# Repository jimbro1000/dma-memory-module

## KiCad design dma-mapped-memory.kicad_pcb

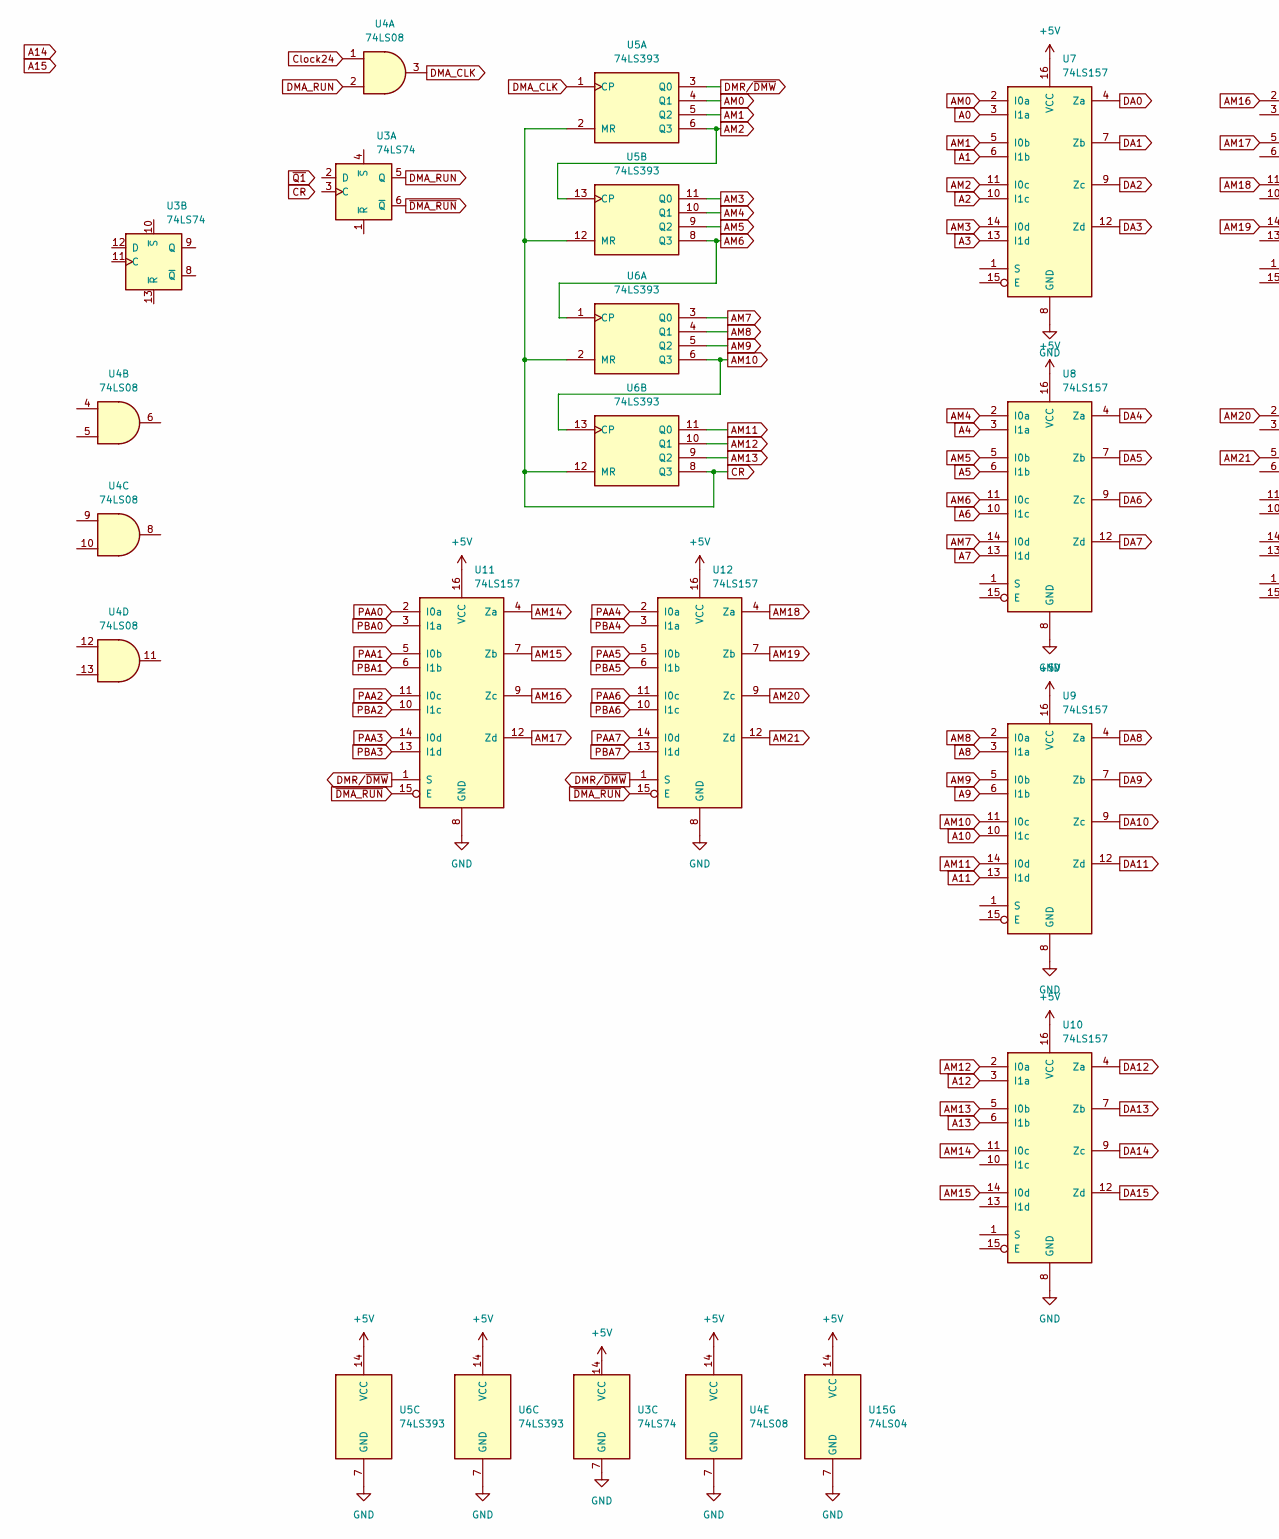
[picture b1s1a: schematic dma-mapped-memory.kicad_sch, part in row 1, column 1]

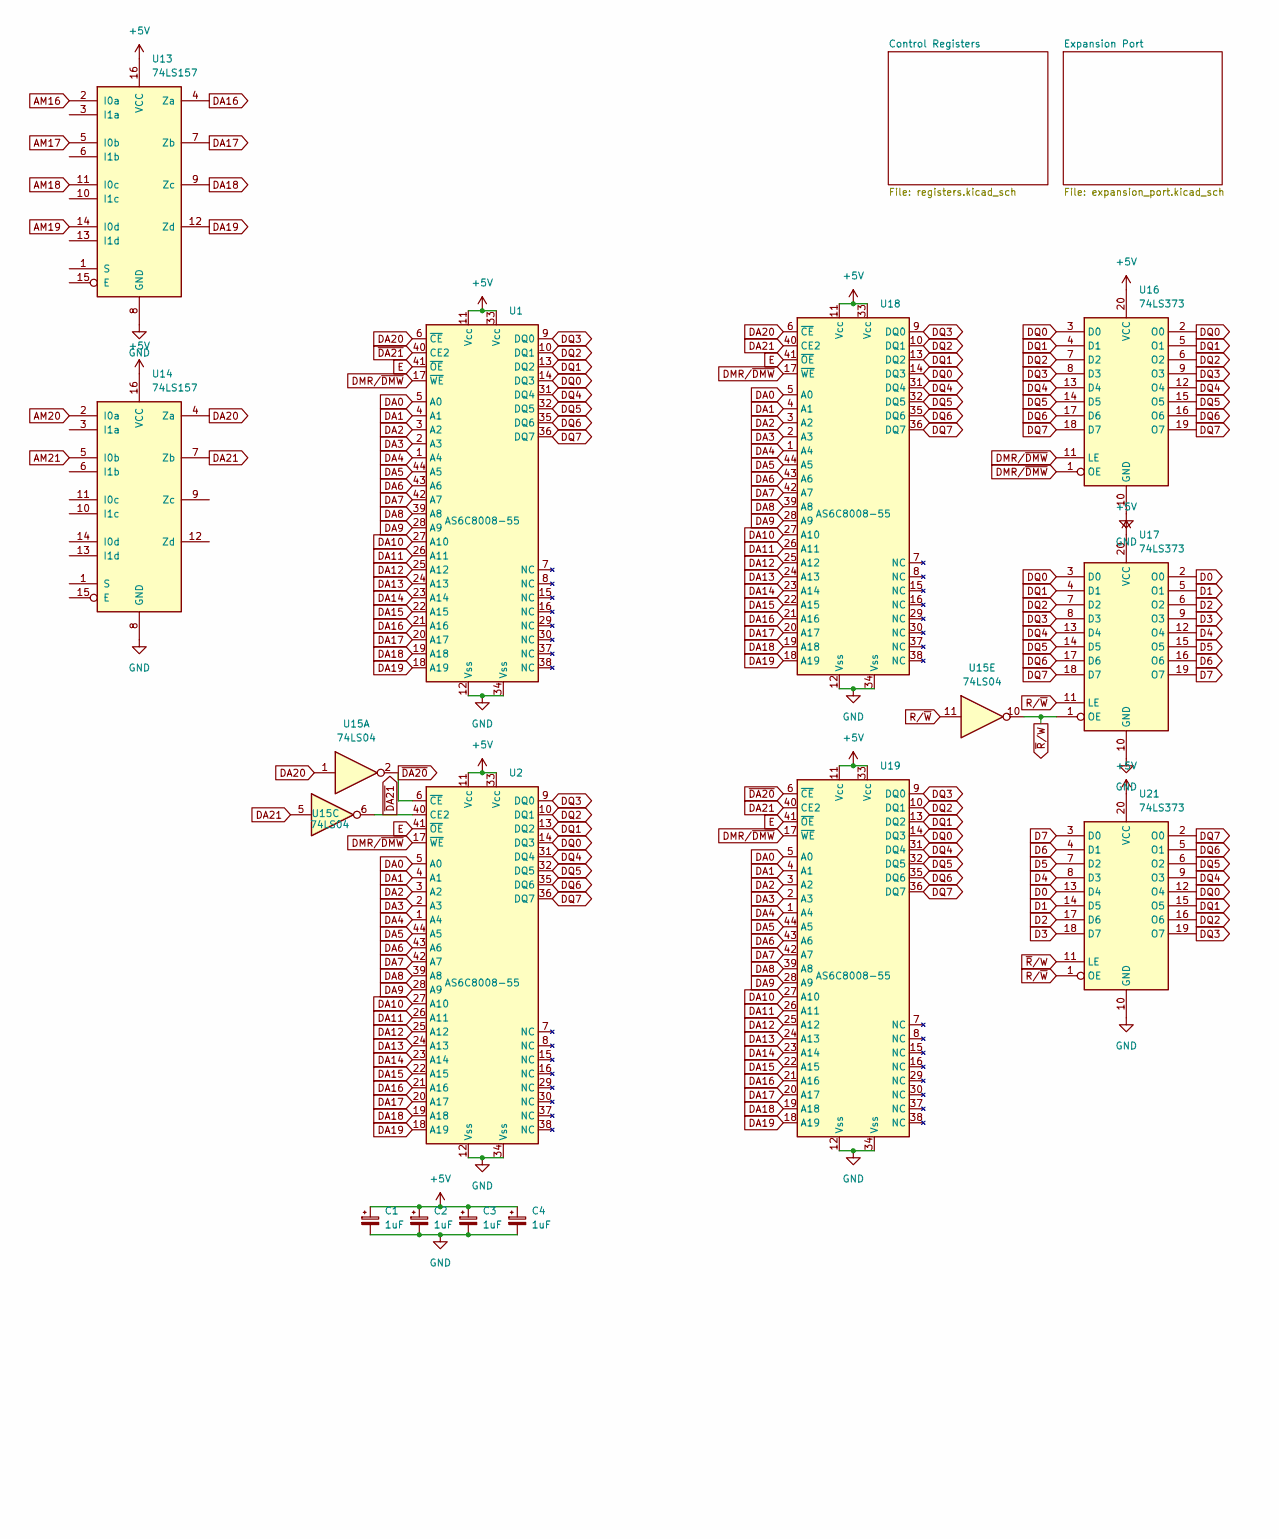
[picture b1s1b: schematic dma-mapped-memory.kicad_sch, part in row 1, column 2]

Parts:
C1, C2, C3, C4: 1uF; CP_EIA-3216-18_Kemet-A_Pad1.58x1.35mm_HandSolder
U1, U2, U18, U19: AS6C8008-55; TSOP-II-44_10.16x18.41mm_P0.8mm
U3: 74LS74; SOIC-14_3.9x8.7mm_P1.27mm
U4: 74LS08; SOIC-14_3.9x8.7mm_P1.27mm
U5, U6: 74LS393; SOIC-14_3.9x8.7mm_P1.27mm
U7, U8, U9, U10, U11, U12, U13, U14: 74LS157; SOIC-16_3.9x9.9mm_P1.27mm
U15: 74LS04; SOIC-14_3.9x8.7mm_P1.27mm
U16, U17, U21: 74LS373; SOIC-20W_7.5x12.8mm_P1.27mm

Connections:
+5V: C1.1, C2.1, C3.1, C4.1, U1.11 (Vcc), U1.33 (Vcc), U2.11 (Vcc), U2.33 (Vcc), U3.14 (VCC), U4.14 (VCC), U5.14 (VCC), U6.14 (VCC), U7.16 (VCC), U8.16 (VCC), U9.16 (VCC), U10.16 (VCC), U11.16 (VCC), U12.16 (VCC), U13.16 (VCC), U14.16 (VCC), U15.14 (VCC), U16.20 (VCC), U17.20 (VCC), U18.11 (Vcc), U18.33 (Vcc), U19.11 (Vcc), U19.33 (Vcc), U21.20 (VCC); also elsewhere on the board
A0: U7.3 (I1a); also elsewhere on the board
A1: U7.6 (I1b); also elsewhere on the board
A2: U7.10 (I1c); also elsewhere on the board
A3: U7.13 (I1d); also elsewhere on the board
A4: U8.3 (I1a); also elsewhere on the board
A5: U8.6 (I1b); also elsewhere on the board
A6: U8.10 (I1c); also elsewhere on the board
A7: U8.13 (I1d); also elsewhere on the board
A8: U9.3 (I1a); also elsewhere on the board
A9: U9.6 (I1b); also elsewhere on the board
A10: U9.10 (I1c); also elsewhere on the board
A11: U9.13 (I1d); also elsewhere on the board
A12: U10.3 (I1a); also elsewhere on the board
A13: U10.6 (I1b); also elsewhere on the board
AM0: U5.4 (Q1), U7.2 (I0a)
AM1: U5.5 (Q2), U7.5 (I0b)
AM2: U5.6 (Q3), U5.13 (CP), U7.11 (I0c)
AM3: U5.11 (Q0), U7.14 (I0d)
AM4: U5.10 (Q1), U8.2 (I0a)
AM5: U5.9 (Q2), U8.5 (I0b)
AM6: U5.8 (Q3), U6.1 (CP), U8.11 (I0c)
AM7: U6.3 (Q0), U8.14 (I0d)
AM8: U6.4 (Q1), U9.2 (I0a)
AM9: U6.5 (Q2), U9.5 (I0b)
AM10: U6.6 (Q3), U6.13 (CP), U9.11 (I0c)
AM11: U6.11 (Q0), U9.14 (I0d)
AM12: U6.10 (Q1), U10.2 (I0a)
AM13: U6.9 (Q2), U10.5 (I0b)
AM14: U10.11 (I0c), U11.4 (Za)
AM15: U10.14 (I0d), U11.7 (Zb)
AM16: U11.9 (Zc), U13.2 (I0a)
AM17: U11.12 (Zd), U13.5 (I0b)
AM18: U12.4 (Za), U13.11 (I0c)
AM19: U12.7 (Zb), U13.14 (I0d)
AM20: U12.9 (Zc), U14.2 (I0a)
AM21: U12.12 (Zd), U14.5 (I0b)
CR: U5.2 (MR), U5.12 (MR), U6.2 (MR), U6.8 (Q3), U6.12 (MR)
Clock24: U4.1; also elsewhere on the board
D0: U17.2 (O0), U21.13 (D4); also elsewhere on the board
D1: U17.5 (O1), U21.14 (D5); also elsewhere on the board
D2: U17.6 (O2), U21.17 (D6); also elsewhere on the board
D3: U17.9 (O3), U21.18 (D7); also elsewhere on the board
D4: U17.12 (O4), U21.8 (D3); also elsewhere on the board
D5: U17.15 (O5), U21.7 (D2); also elsewhere on the board
D6: U17.16 (O6), U21.4 (D1); also elsewhere on the board
D7: U17.19 (O7), U21.3 (D0); also elsewhere on the board
DA0: U1.5 (A0), U2.5 (A0), U7.4 (Za), U18.5 (A0), U19.5 (A0)
DA1: U1.4 (A1), U2.4 (A1), U7.7 (Zb), U18.4 (A1), U19.4 (A1)
DA2: U1.3 (A2), U2.3 (A2), U7.9 (Zc), U18.3 (A2), U19.3 (A2)
DA3: U1.2 (A3), U2.2 (A3), U7.12 (Zd), U18.2 (A3), U19.2 (A3)
DA4: U1.1 (A4), U2.1 (A4), U8.4 (Za), U18.1 (A4), U19.1 (A4)
DA5: U1.44 (A5), U2.44 (A5), U8.7 (Zb), U18.44 (A5), U19.44 (A5)
DA6: U1.43 (A6), U2.43 (A6), U8.9 (Zc), U18.43 (A6), U19.43 (A6)
DA7: U1.42 (A7), U2.42 (A7), U8.12 (Zd), U18.42 (A7), U19.42 (A7)
DA8: U1.39 (A8), U2.39 (A8), U9.4 (Za), U18.39 (A8), U19.39 (A8)
DA9: U1.28 (A9), U2.28 (A9), U9.7 (Zb), U18.28 (A9), U19.28 (A9)
DA10: U1.27 (A10), U2.27 (A10), U9.9 (Zc), U18.27 (A10), U19.27 (A10)
DA11: U1.26 (A11), U2.26 (A11), U9.12 (Zd), U18.26 (A11), U19.26 (A11)
DA12: U1.25 (A12), U2.25 (A12), U10.4 (Za), U18.25 (A12), U19.25 (A12)
DA13: U1.24 (A13), U2.24 (A13), U10.7 (Zb), U18.24 (A13), U19.24 (A13)
DA14: U1.23 (A14), U2.23 (A14), U10.9 (Zc), U18.23 (A14), U19.23 (A14)
DA15: U1.22 (A15), U2.22 (A15), U10.12 (Zd), U18.22 (A15), U19.22 (A15)
DA16: U1.21 (A16), U2.21 (A16), U13.4 (Za), U18.21 (A16), U19.21 (A16)
DA17: U1.20 (A17), U2.20 (A17), U13.7 (Zb), U18.20 (A17), U19.20 (A17)
DA18: U1.19 (A18), U2.19 (A18), U13.9 (Zc), U18.19 (A18), U19.19 (A18)
DA19: U1.18 (A19), U2.18 (A19), U13.12 (Zd), U18.18 (A19), U19.18 (A19)
DA20: U1.6 (~CE), U14.4 (Za), U15.1, U18.6 (~CE)
DA21: U14.7 (Zb), U15.5, U18.40 (CE2), U19.40 (CE2)
DMA_CLK: U4.3, U5.1 (CP)
DMA_RUN: U3.5 (Q), U4.2
DMR/~DMW: U1.17 (~WE), U2.17 (~WE), U5.3 (Q0), U11.1 (S), U12.1 (S), U16.1 (OE), U16.11 (LE), U18.17 (~WE), U19.17 (~WE)
DQ0: U1.14 (DQ3), U2.14 (DQ3), U16.2 (O0), U16.3 (D0), U17.3 (D0), U18.14 (DQ3), U19.14 (DQ3), U21.12 (O4)
DQ1: U1.13 (DQ2), U2.13 (DQ2), U16.4 (D1), U16.5 (O1), U17.4 (D1), U18.13 (DQ2), U19.13 (DQ2), U21.15 (O5)
DQ2: U1.10 (DQ1), U2.10 (DQ1), U16.6 (O2), U16.7 (D2), U17.7 (D2), U18.10 (DQ1), U19.10 (DQ1), U21.16 (O6)
DQ3: U1.9 (DQ0), U2.9 (DQ0), U16.8 (D3), U16.9 (O3), U17.8 (D3), U18.9 (DQ0), U19.9 (DQ0), U21.19 (O7)
DQ4: U1.31 (DQ4), U2.31 (DQ4), U16.12 (O4), U16.13 (D4), U17.13 (D4), U18.31 (DQ4), U19.31 (DQ4), U21.9 (O3)
DQ5: U1.32 (DQ5), U2.32 (DQ5), U16.14 (D5), U16.15 (O5), U17.14 (D5), U18.32 (DQ5), U19.32 (DQ5), U21.6 (O2)
DQ6: U1.35 (DQ6), U2.35 (DQ6), U16.16 (O6), U16.17 (D6), U17.17 (D6), U18.35 (DQ6), U19.35 (DQ6), U21.5 (O1)
DQ7: U1.36 (DQ7), U2.36 (DQ7), U16.18 (D7), U16.19 (O7), U17.18 (D7), U18.36 (DQ7), U19.36 (DQ7), U21.2 (O0)
E: U1.41 (~OE), U2.41 (~OE), U18.41 (~OE), U19.41 (~OE); also elsewhere on the board
GND: C1.2, C2.2, C3.2, C4.2, U1.12 (Vss), U1.34 (Vss), U2.12 (Vss), U2.34 (Vss), U3.7 (GND), U4.7 (GND), U5.7 (GND), U6.7 (GND), U7.8 (GND), U8.8 (GND), U9.8 (GND), U10.8 (GND), U11.8 (GND), U12.8 (GND), U13.8 (GND), U14.8 (GND), U15.7 (GND), U16.10 (GND), U17.10 (GND), U18.12 (Vss), U18.34 (Vss), U19.12 (Vss), U19.34 (Vss), U21.10 (GND); also elsewhere on the board
PAA0: U11.2 (I0a); also elsewhere on the board
PAA1: U11.5 (I0b); also elsewhere on the board
PAA2: U11.11 (I0c); also elsewhere on the board
PAA3: U11.14 (I0d); also elsewhere on the board
PAA4: U12.2 (I0a); also elsewhere on the board
PAA5: U12.5 (I0b); also elsewhere on the board
PAA6: U12.11 (I0c); also elsewhere on the board
PAA7: U12.14 (I0d); also elsewhere on the board
PBA0: U11.3 (I1a); also elsewhere on the board
PBA1: U11.6 (I1b); also elsewhere on the board
PBA2: U11.10 (I1c); also elsewhere on the board
PBA3: U11.13 (I1d); also elsewhere on the board
PBA4: U12.3 (I1a); also elsewhere on the board
PBA5: U12.6 (I1b); also elsewhere on the board
PBA6: U12.10 (I1c); also elsewhere on the board
PBA7: U12.13 (I1d); also elsewhere on the board
R/~W: U15.11, U17.11 (LE), U21.1 (OE); also elsewhere on the board
~DA20: U2.6 (~CE), U15.2, U19.6 (~CE)
~DA21: U1.40 (CE2), U2.40 (CE2), U15.6
~DMA_RUN: U3.6 (~Q), U11.15 (E), U12.15 (E)
~R/W: U15.10, U17.1 (OE), U21.11 (LE); also elsewhere on the board

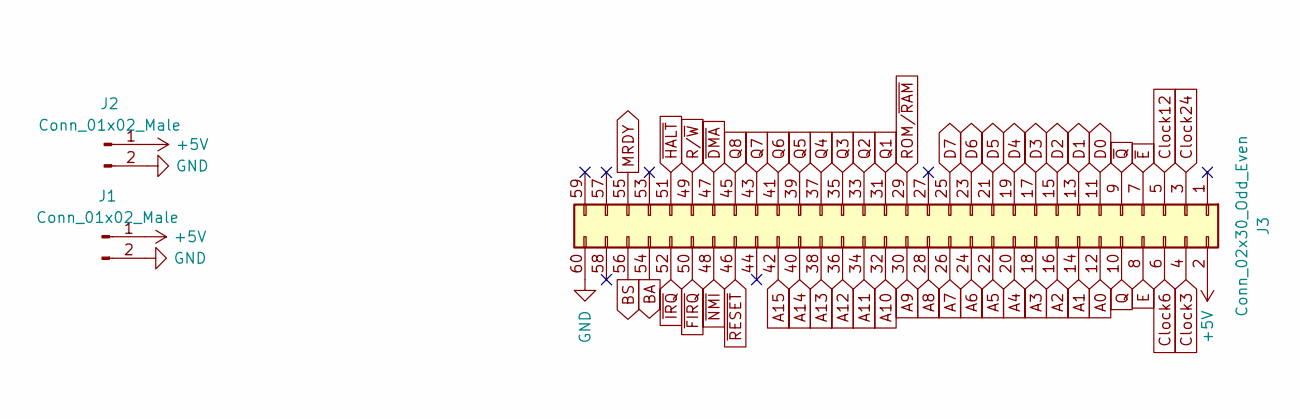
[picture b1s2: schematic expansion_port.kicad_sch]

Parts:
J1, J2: Conn_01x02_Male; PinHeader_1x02_P2.54mm_Vertical
J3: Conn_02x30_Odd_Even; PinHeader_2x30_P2.54mm_Vertical

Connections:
+5V: J1.1, J2.1, J3.2; also elsewhere on the board
A0: J3.12; also elsewhere on the board
A1: J3.14; also elsewhere on the board
A2: J3.16; also elsewhere on the board
A3: J3.18; also elsewhere on the board
A4: J3.20; also elsewhere on the board
A5: J3.22; also elsewhere on the board
A6: J3.24; also elsewhere on the board
A7: J3.26; also elsewhere on the board
A8: J3.28; also elsewhere on the board
A9: J3.30; also elsewhere on the board
A10: J3.32; also elsewhere on the board
A11: J3.34; also elsewhere on the board
A12: J3.36; also elsewhere on the board
A13: J3.38; also elsewhere on the board
A14: J3.40; also elsewhere on the board
A15: J3.42; also elsewhere on the board
BA: J3.54
BS: J3.56
Clock3: J3.4
Clock6: J3.6
Clock12: J3.5
Clock24: J3.3; also elsewhere on the board
D0: J3.11; also elsewhere on the board
D1: J3.13; also elsewhere on the board
D2: J3.15; also elsewhere on the board
D3: J3.17; also elsewhere on the board
D4: J3.19; also elsewhere on the board
D5: J3.21; also elsewhere on the board
D6: J3.23; also elsewhere on the board
D7: J3.25; also elsewhere on the board
E: J3.8; also elsewhere on the board
GND: J1.2, J2.2, J3.60; also elsewhere on the board
MRDY: J3.55
Q: J3.10
Q1: J3.31
Q2: J3.33
Q3: J3.35
Q4: J3.37
Q5: J3.39
Q6: J3.41
Q7: J3.43
Q8: J3.45
ROM/~RAM: J3.29
R/~W: J3.49; also elsewhere on the board
~DMA: J3.47
~E: J3.7
~FIRQ: J3.50
~HALT: J3.51
~IRQ: J3.52
~NMI: J3.48
~Q: J3.9
~RESET: J3.46

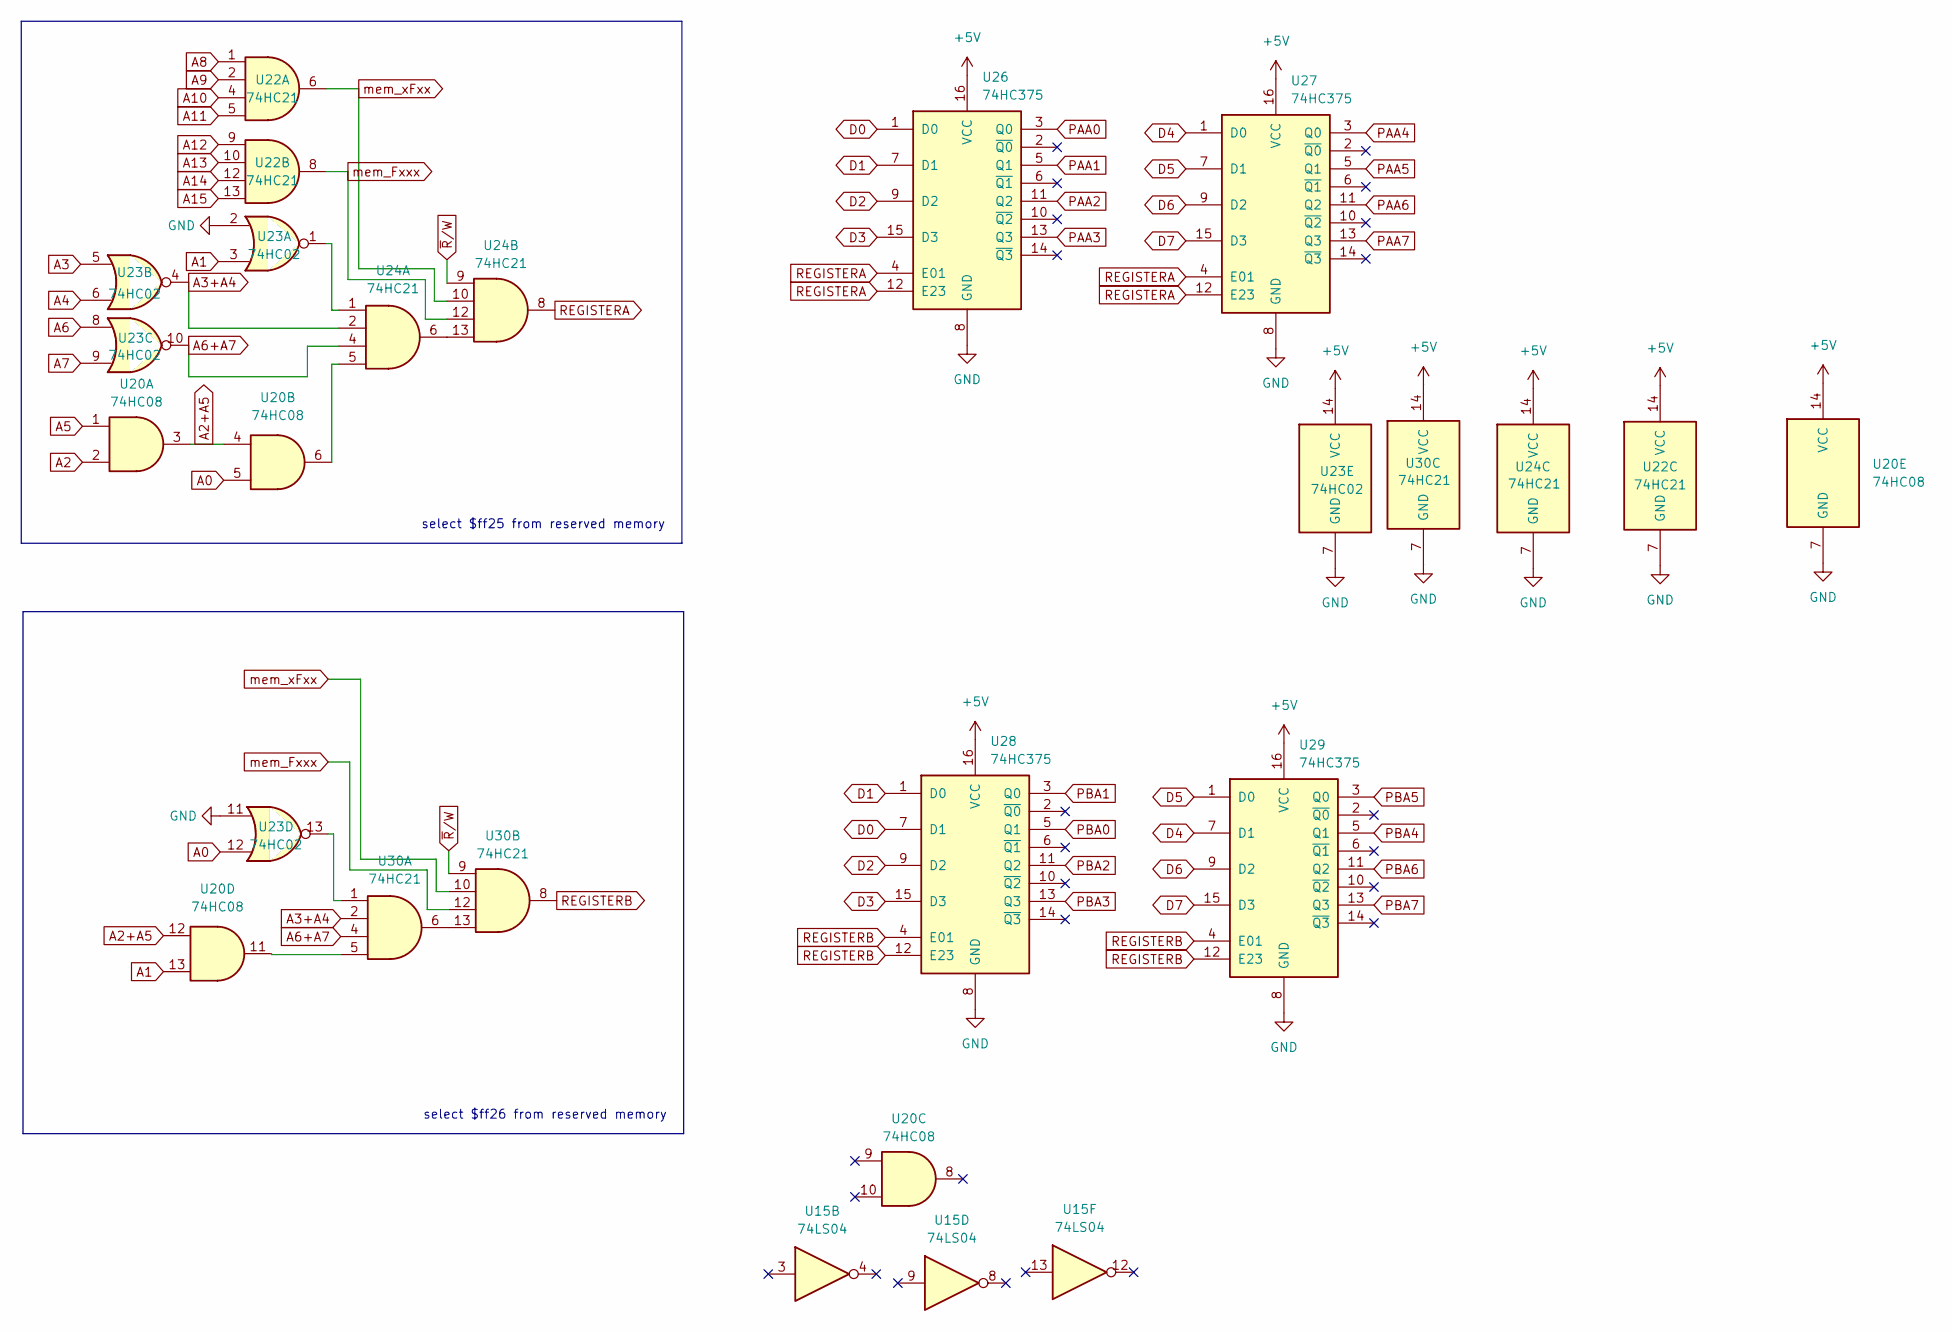
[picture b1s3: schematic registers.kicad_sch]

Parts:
U15: 74LS04; SOIC-14_3.9x8.7mm_P1.27mm
U20: 74HC08; SO-14_3.9x8.65mm_P1.27mm
U22, U24, U30: 74HC21; SO-14_3.9x8.65mm_P1.27mm
U23: 74HC02; SO-14_3.9x8.65mm_P1.27mm
U26, U27, U28, U29: 74HC375; SO-16_3.9x9.9mm_P1.27mm

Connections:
+5V: U15.14 (VCC), U20.14 (VCC), U22.14 (VCC), U23.14 (VCC), U24.14 (VCC), U26.16 (VCC), U27.16 (VCC), U28.16 (VCC), U29.16 (VCC), U30.14 (VCC); also elsewhere on the board
A0: U20.5, U23.12; also elsewhere on the board
A1: U20.13, U23.3; also elsewhere on the board
A2: U20.2; also elsewhere on the board
A2+A5: U20.3, U20.4, U20.12
A3: U23.5; also elsewhere on the board
A3+A4: U23.4, U24.2, U30.2
A4: U23.6; also elsewhere on the board
A5: U20.1; also elsewhere on the board
A6: U23.8; also elsewhere on the board
A6+A7: U23.10, U24.4, U30.4
A7: U23.9; also elsewhere on the board
A8: U22.1; also elsewhere on the board
A9: U22.2; also elsewhere on the board
A10: U22.4; also elsewhere on the board
A11: U22.5; also elsewhere on the board
A12: U22.9; also elsewhere on the board
A13: U22.10; also elsewhere on the board
A14: U22.12; also elsewhere on the board
A15: U22.13; also elsewhere on the board
D0: U26.1 (D0), U28.7 (D1); also elsewhere on the board
D1: U26.7 (D1), U28.1 (D0); also elsewhere on the board
D2: U26.9 (D2), U28.9 (D2); also elsewhere on the board
D3: U26.15 (D3), U28.15 (D3); also elsewhere on the board
D4: U27.1 (D0), U29.7 (D1); also elsewhere on the board
D5: U27.7 (D1), U29.1 (D0); also elsewhere on the board
D6: U27.9 (D2), U29.9 (D2); also elsewhere on the board
D7: U27.15 (D3), U29.15 (D3); also elsewhere on the board
DA20: U15.1; also elsewhere on the board
DA21: U15.5; also elsewhere on the board
GND: U15.7 (GND), U20.7 (GND), U22.7 (GND), U23.2, U23.7 (GND), U23.11, U24.7 (GND), U26.8 (GND), U27.8 (GND), U28.8 (GND), U29.8 (GND), U30.7 (GND); also elsewhere on the board
unnamed: U20.6, U24.5
unnamed: U20.11, U30.5
unnamed: U23.1, U24.1
unnamed: U23.13, U30.1
unnamed: U24.6, U24.13
unnamed: U30.6, U30.13
PAA0: U26.3 (Q0); also elsewhere on the board
PAA1: U26.5 (Q1); also elsewhere on the board
PAA2: U26.11 (Q2); also elsewhere on the board
PAA3: U26.13 (Q3); also elsewhere on the board
PAA4: U27.3 (Q0); also elsewhere on the board
PAA5: U27.5 (Q1); also elsewhere on the board
PAA6: U27.11 (Q2); also elsewhere on the board
PAA7: U27.13 (Q3); also elsewhere on the board
PBA0: U28.5 (Q1); also elsewhere on the board
PBA1: U28.3 (Q0); also elsewhere on the board
PBA2: U28.11 (Q2); also elsewhere on the board
PBA3: U28.13 (Q3); also elsewhere on the board
PBA4: U29.5 (Q1); also elsewhere on the board
PBA5: U29.3 (Q0); also elsewhere on the board
PBA6: U29.11 (Q2); also elsewhere on the board
PBA7: U29.13 (Q3); also elsewhere on the board
REGISTERA: U24.8, U26.4 (E01), U26.12 (E23), U27.4 (E01), U27.12 (E23)
REGISTERB: U28.4 (E01), U28.12 (E23), U29.4 (E01), U29.12 (E23), U30.8
R/~W: U15.11; also elsewhere on the board
mem_Fxxx: U22.8, U24.12, U30.12
mem_xFxx: U22.6, U24.10, U30.10
~DA20: U15.2; also elsewhere on the board
~DA21: U15.6; also elsewhere on the board
~R/W: U15.10, U24.9, U30.9; also elsewhere on the board

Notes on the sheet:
select $ff25 from reserved memory
select $ff26 from reserved memory

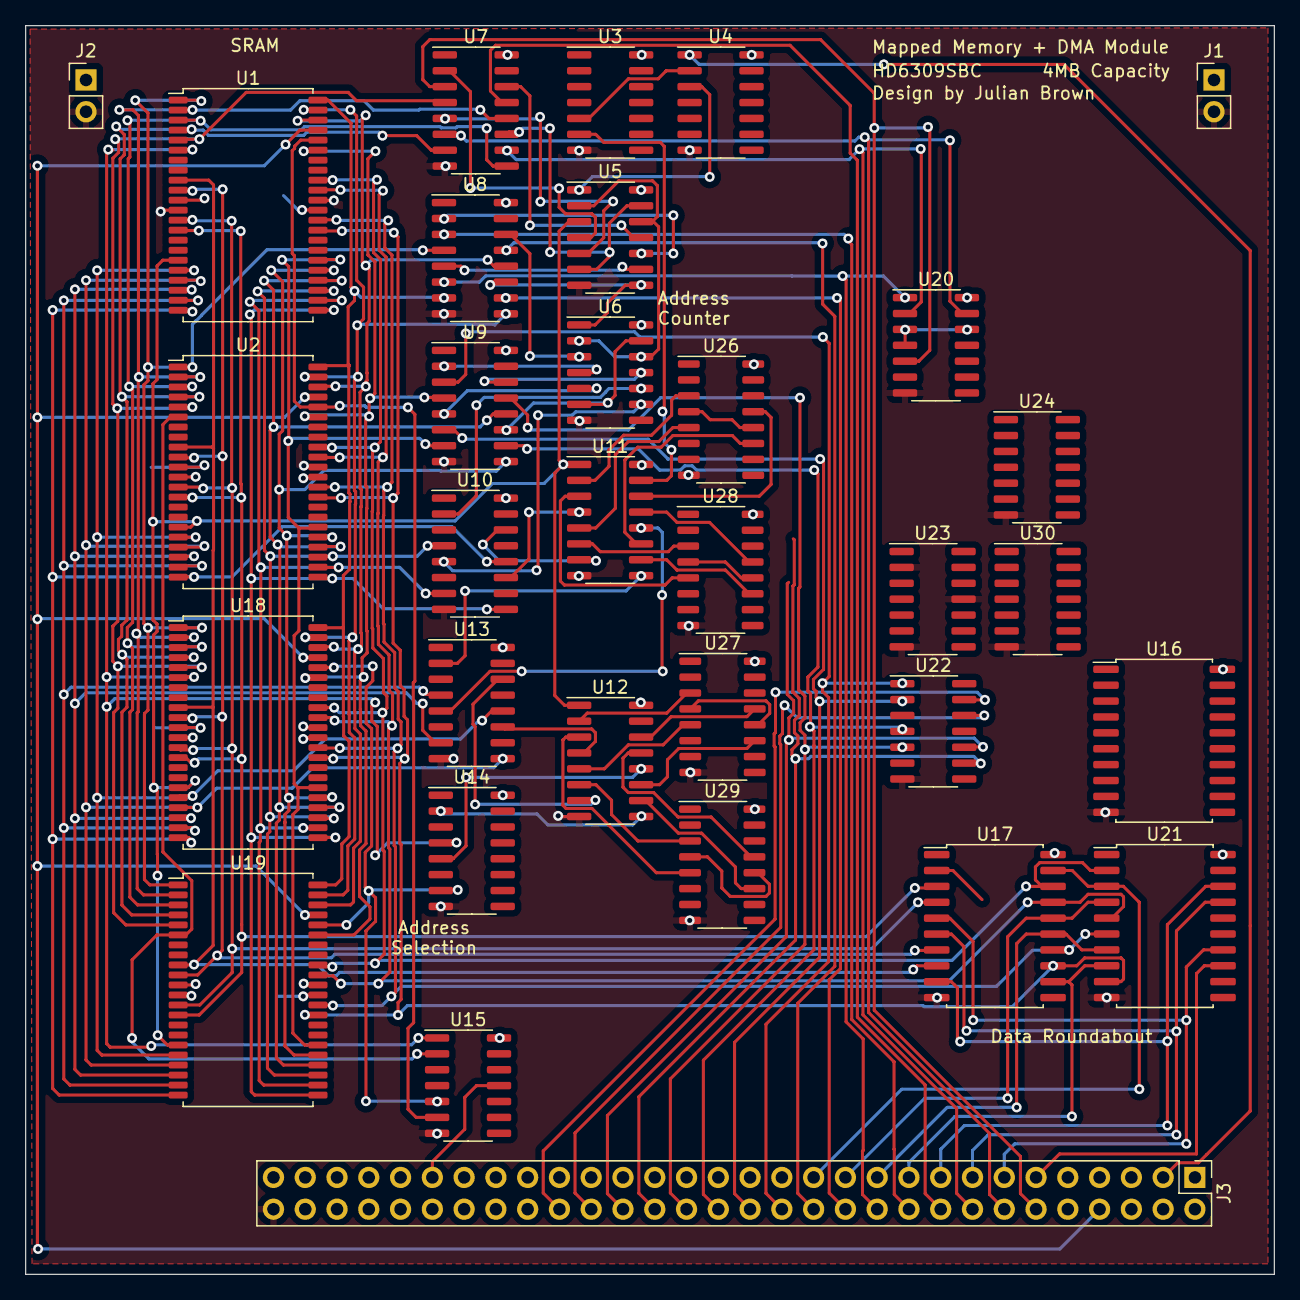
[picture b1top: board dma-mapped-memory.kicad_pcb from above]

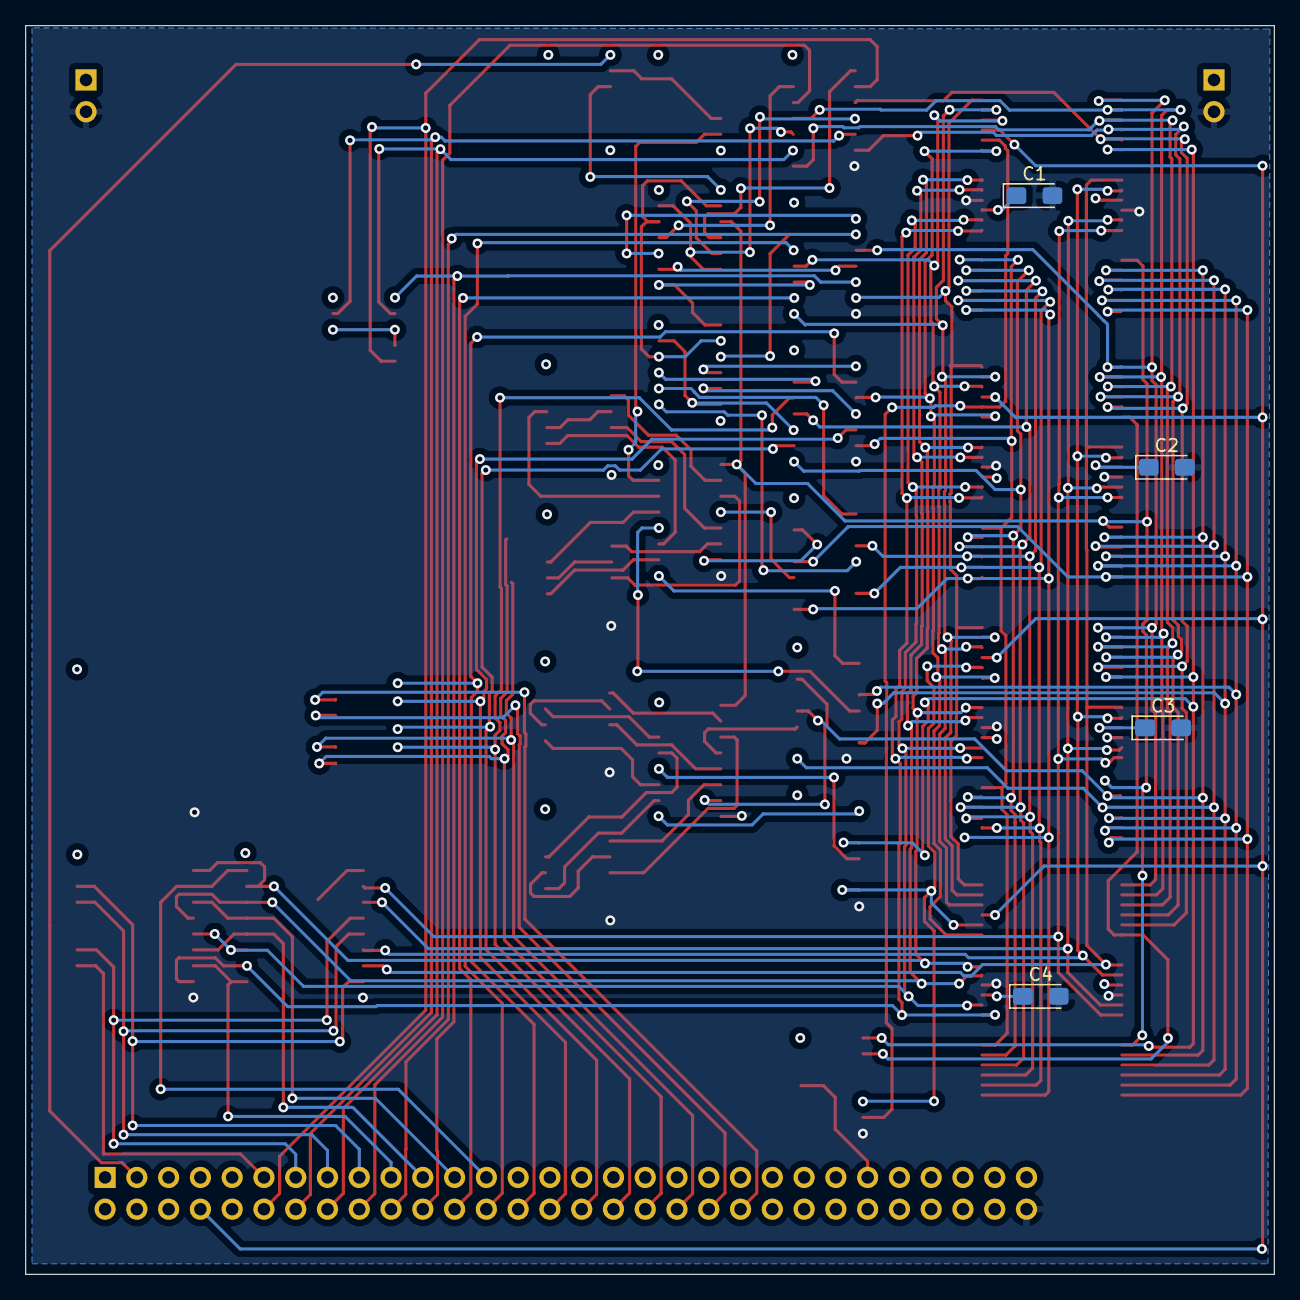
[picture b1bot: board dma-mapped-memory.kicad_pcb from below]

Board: 4 copper layers, 99.8 x 99.8 mm, 36 parts (4 on the bottom side), 118 nets.

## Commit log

2023-11-02 add address registers
2023-11-03 simplify logic
2023-11-03 continue hand tracing
2023-11-04 add addressing
